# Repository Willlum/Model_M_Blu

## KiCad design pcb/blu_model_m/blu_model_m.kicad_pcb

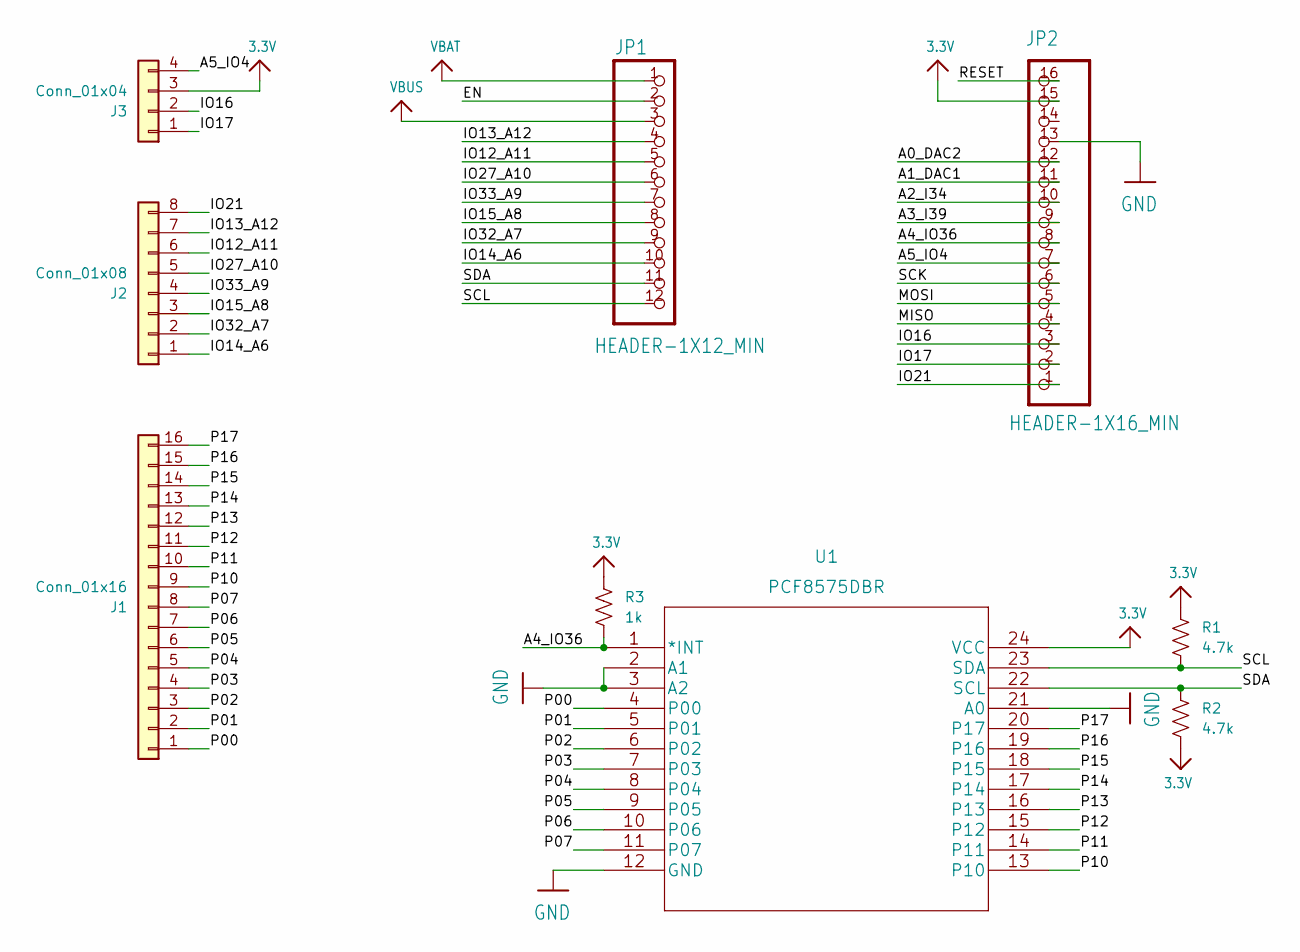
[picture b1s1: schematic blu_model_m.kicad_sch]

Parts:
J1: Conn_01x16; PinSocket_1x16_P2.54mm_Vertical
J2: Conn_01x08; PinSocket_1x08_P2.54mm_Vertical
J3: Conn_01x04; PinSocket_1x04_P2.54mm_Vertical
JP1: HEADER-1X12_MIN; PinSocket_1x12_P2.54mm_Vertical
JP2: HEADER-1X16_MIN; PinSocket_1x16_P2.54mm_Vertical
R1, R2: 4.7k; R_0805_2012Metric_Pad1.20x1.40mm_HandSolder
R3: 1k; R_0805_2012Metric_Pad1.20x1.40mm_HandSolder
U1: PCF8575DBR; SSOP-24_5.3x8.2mm_P0.65mm

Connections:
3.3V: J3.3, JP2.15, R1.1, R2.2, R3.1, U1.24 (VCC)
/A0_DAC2: JP2.12
/A1_DAC1: JP2.11
/A2_I34: JP2.10
/A3_I39: JP2.9
/A4_IO36: JP2.8, R3.2, U1.1 (*INT)
/A5_IO4: J3.4, JP2.7
/EN: JP1.2
/IO12_A11: J2.6, JP1.5
/IO13_A12: J2.7, JP1.4
/IO14_A6: J2.1, JP1.10
/IO15_A8: J2.3, JP1.8
/IO16: J3.2, JP2.3
/IO17: J3.1, JP2.2
/IO21: J2.8, JP2.1
/IO27_A10: J2.5, JP1.6
/IO32_A7: J2.2, JP1.9
/IO33_A9: J2.4, JP1.7
/MISO: JP2.4
/MOSI: JP2.5
/P00: J1.1, U1.4 (P00)
/P01: J1.2, U1.5 (P01)
/P02: J1.3, U1.6 (P02)
/P03: J1.4, U1.7 (P03)
/P04: J1.5, U1.8 (P04)
/P05: J1.6, U1.9 (P05)
/P06: J1.7, U1.10 (P06)
/P07: J1.8, U1.11 (P07)
/P10: J1.9, U1.13 (P10)
/P11: J1.10, U1.14 (P11)
/P12: J1.11, U1.15 (P12)
/P13: J1.12, U1.16 (P13)
/P14: J1.13, U1.17 (P14)
/P15: J1.14, U1.18 (P15)
/P16: J1.15, U1.19 (P16)
/P17: J1.16, U1.20 (P17)
/RESET: JP2.16
/SCK: JP2.6
/SCL: JP1.12, R1.2, U1.23 (SDA)
/SDA: JP1.11, R2.1, U1.22 (SCL)
GND: JP2.13, U1.2 (A1), U1.3 (A2), U1.12 (GND), U1.21 (A0)
VBAT: JP1.1
VBUS: JP1.3

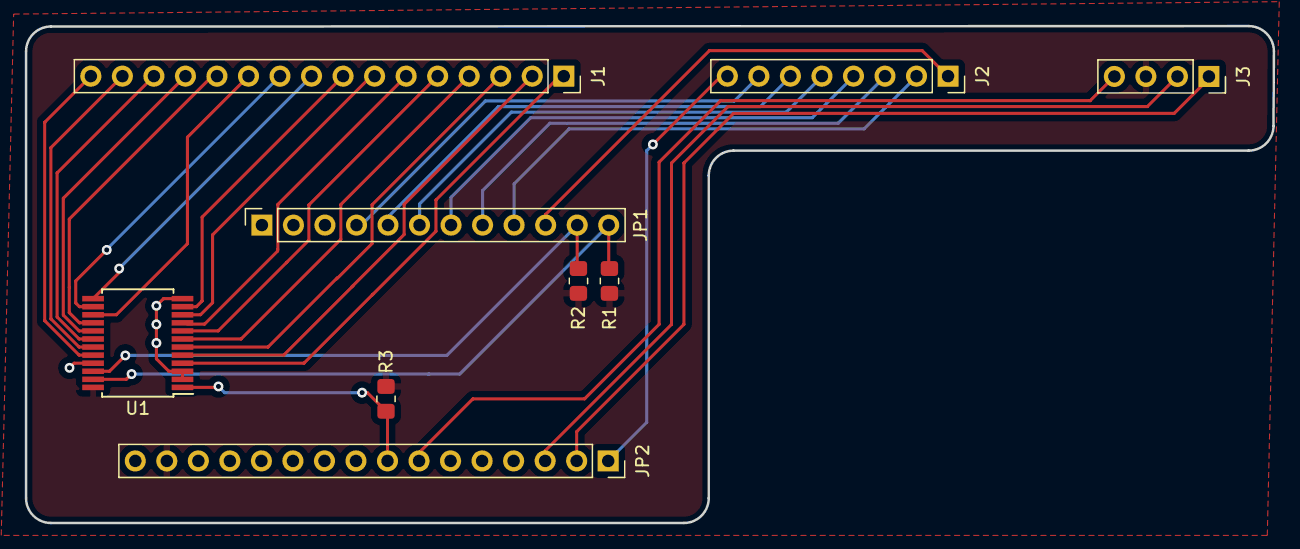
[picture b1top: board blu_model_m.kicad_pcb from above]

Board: 2 copper layers, 100.5 x 40.0 mm, 9 parts (0 on the bottom side), 32 nets.

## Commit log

2023-02-06 init commit
2023-02-06 updated with local version
2023-02-06 changed some keys
2023-02-08 Updated pcb to v1.1. Format changes in code
2023-02-08 Deleted unused folders
2023-02-19 moved and renamed bom
